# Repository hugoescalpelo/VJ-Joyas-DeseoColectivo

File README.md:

# VJ-Joyas-DeseoColectivo
Este repositorio contiene el código de la Máquina de deseo colectivo, un proyecto de VJ-Joyas

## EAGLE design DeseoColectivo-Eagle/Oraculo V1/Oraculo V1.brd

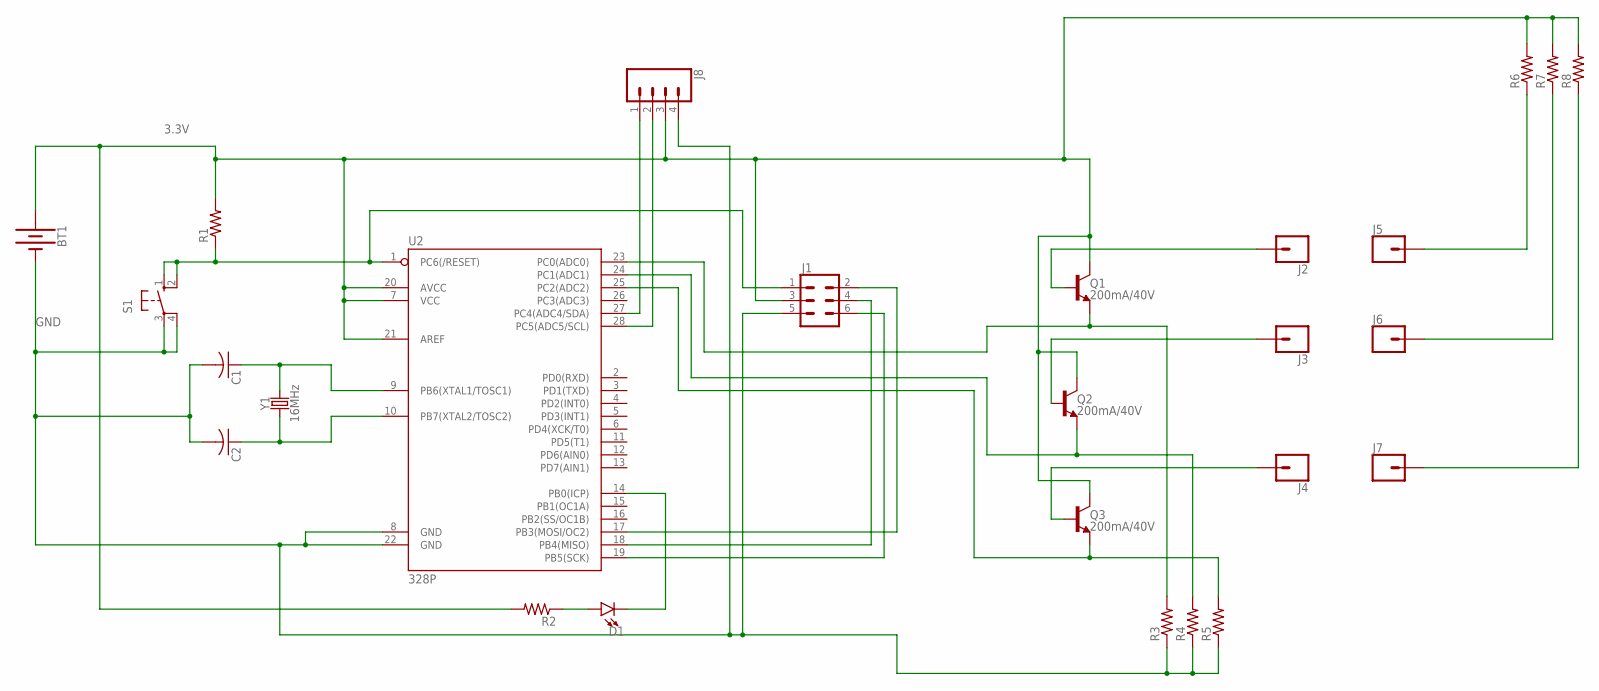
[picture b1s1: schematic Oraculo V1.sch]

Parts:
BT1: BATTERY-20MM_PTH; BATTCOM_20MM_PTH
C1, C2: C-US050-025X075; C050-025X075
D1: LED5MM; LED_5MM
J1: CONN_03X2NO_SILK; 2X3-NS
J2, J3, J4, J5, J6, J7: CONN_01; 1X01
J8: CONN_04; 1X04
Q1, Q2, Q3: 200mA/40V; TO-92
R1, R2, R3, R4, R5, R6, R7, R8: R-US_0204/7; 0204/7
S1: 10-XX; B3F-10XX
U2: 328P; DIP28
Y1: 16MHz; HC49US

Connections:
3.3V: BT1.1 (+), J1.3, J8.3, Q1.3 (C), Q2.3 (C), Q3.3 (C), R1.2, R2.2, R6.2, R7.2, R8.2, U2.7 (VCC), U2.20 (AVCC), U2.21 (AREF)
GND: BT1.2 (-), C1.2, C2.2, J1.5, J8.4, R3.1, R4.1, R5.1, S1.3, S1.4 (P1), U2.8 (GND), U2.22 (GND)
unnamed: C1.1, U2.9 (PB6(XTAL1/TOSC1)), Y1.2
unnamed: C2.1, U2.10 (PB7(XTAL2/TOSC2)), Y1.1
unnamed: J1.1, R1.1, S1.1 (S), S1.2 (S1), U2.1 (PC6(/RESET))
unnamed: J1.2, U2.17 (PB3(MOSI/OC2))
unnamed: D1.K (C), U2.14 (PB0(ICP))
unnamed: J1.6, U2.19 (PB5(SCK))
unnamed: J1.4, U2.18 (PB4(MISO))
unnamed: D1.A, R2.1
unnamed: J8.1, U2.27 (PC4(ADC4/SDA))
unnamed: J2.1, Q1.2 (B)
unnamed: J3.1, Q2.2 (B)
unnamed: J4.1, Q3.2 (B)
unnamed: Q1.1 (E), R3.2, U2.23 (PC0(ADC0))
unnamed: Q2.1 (E), R4.2, U2.24 (PC1(ADC1))
unnamed: Q3.1 (E), R5.2, U2.25 (PC2(ADC2))
unnamed: J5.1, J6.1, J7.1, R6.1, R7.1, R8.1
unnamed: J8.2, U2.28 (PC5(ADC5/SCL))

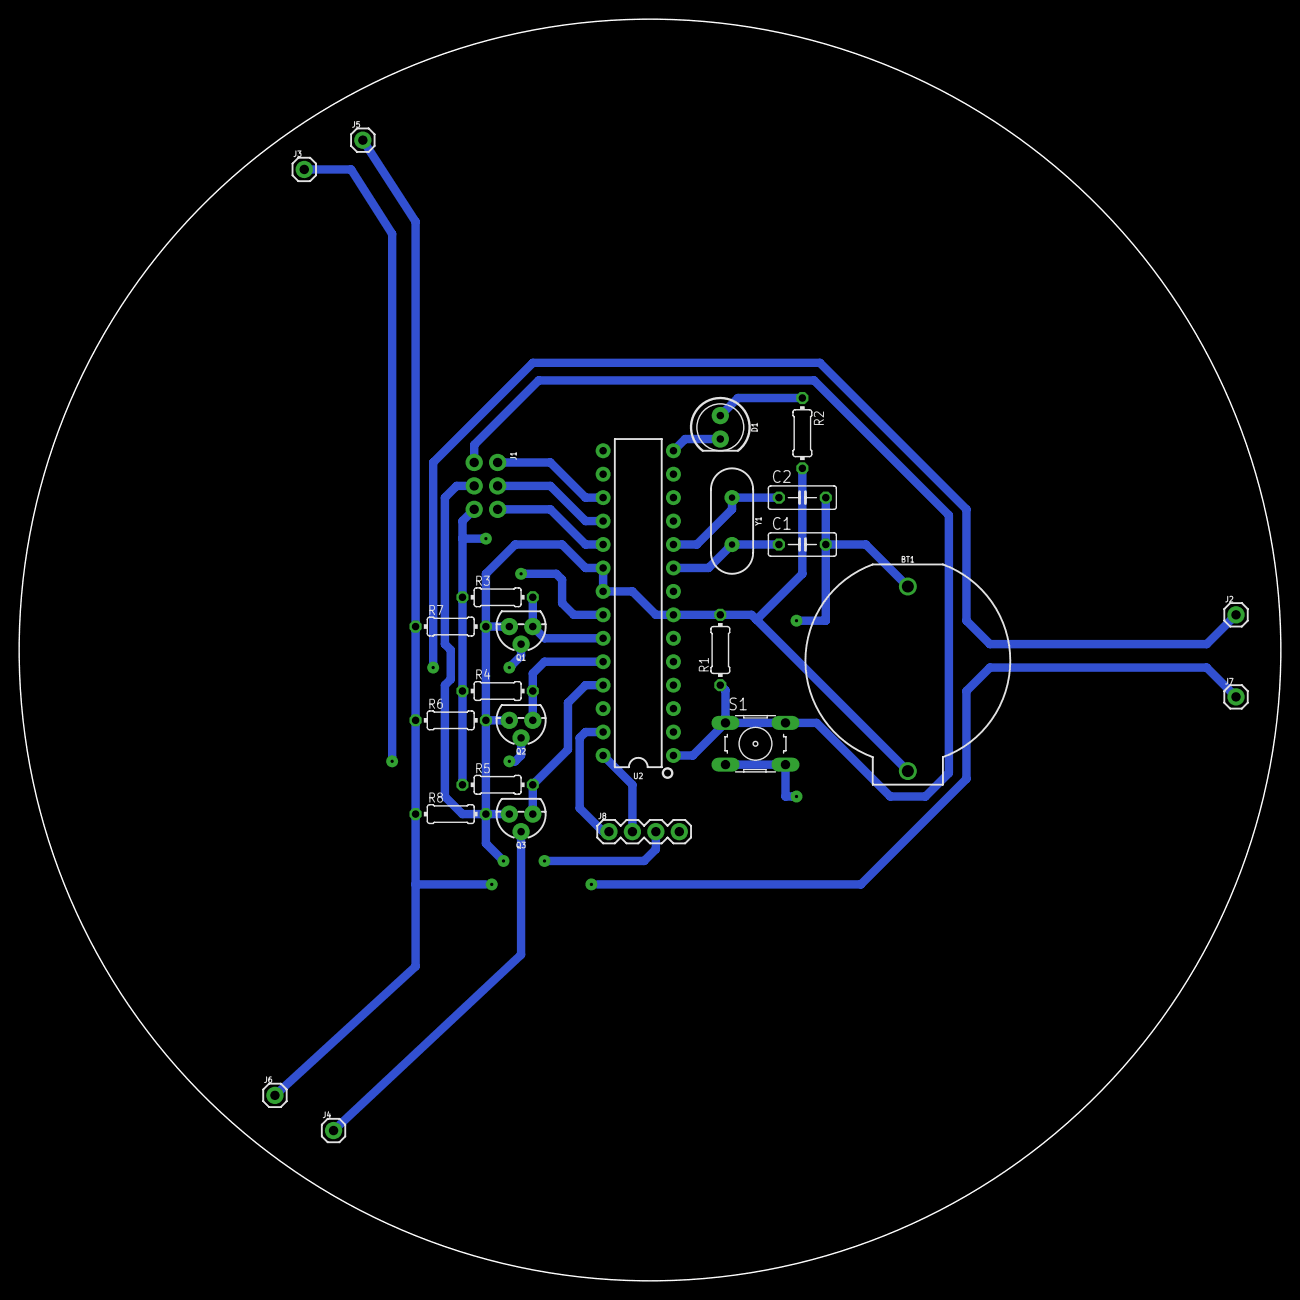
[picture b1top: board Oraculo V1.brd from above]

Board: 2 copper layers, 136.7 x 136.7 mm, 26 parts (0 on the bottom side), 19 nets.

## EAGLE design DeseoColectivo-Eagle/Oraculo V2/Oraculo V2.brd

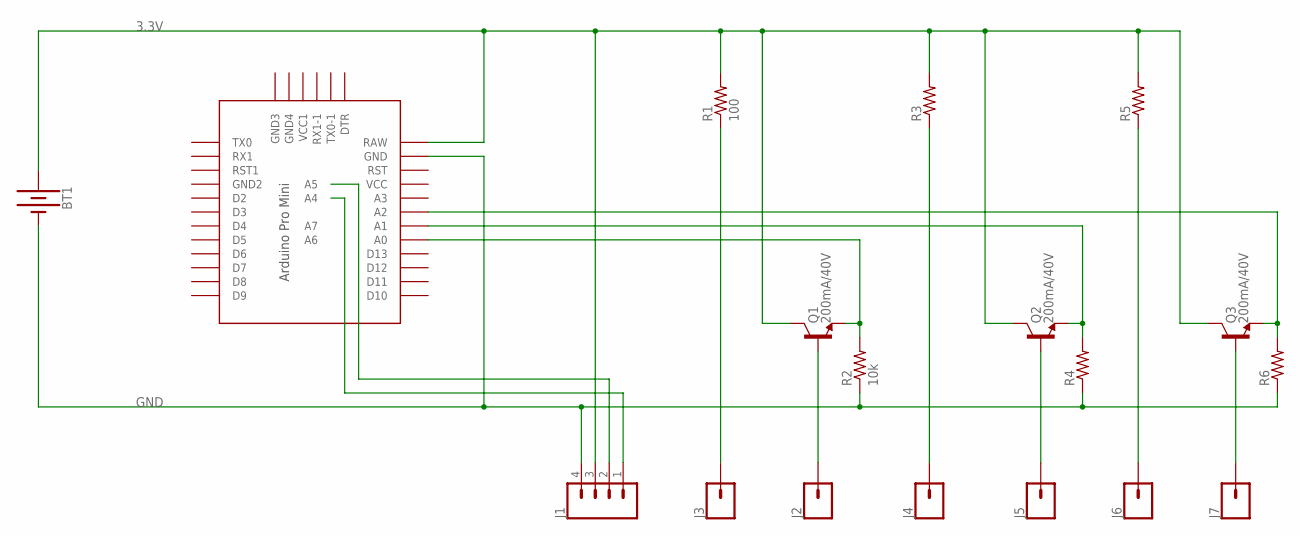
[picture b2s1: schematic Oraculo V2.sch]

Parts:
BT1: BATTERY-20MM_PTH; BATTCOM_20MM_PTH
J1: CONN_04; 1X04
J2, J3, J4, J5, J6, J7: CONN_01PTH_2MM; 1X01_2MM
Q1, Q2, Q3: 200mA/40V; TO-92
R1: 100; 0204/7
R2: 10k; 0204/7
R3, R4, R5, R6: R-US_0204/7; 0204/7
U$1: PRO-MINI-2

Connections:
3.3V: BT1.1 (+), J1.3, Q1.3 (C), Q2.3 (C), Q3.3 (C), R1.2, R3.2, R5.2, U$1.RAW
GND: BT1.2 (-), J1.4, R2.1, R4.1, R6.1, U$1.GND
unnamed: J1.2, U$1.A5
unnamed: J1.1, U$1.A4
unnamed: Q1.1 (E), R2.2, U$1.A0
unnamed: J2.1, Q1.2 (B)
unnamed: J3.1, R1.1
unnamed: J4.1, R3.1
unnamed: J7.1, Q3.2 (B)
unnamed: J5.1, Q2.2 (B)
unnamed: Q2.1 (E), R4.2, U$1.A1
unnamed: Q3.1 (E), R6.2, U$1.A2
unnamed: J6.1, R5.1

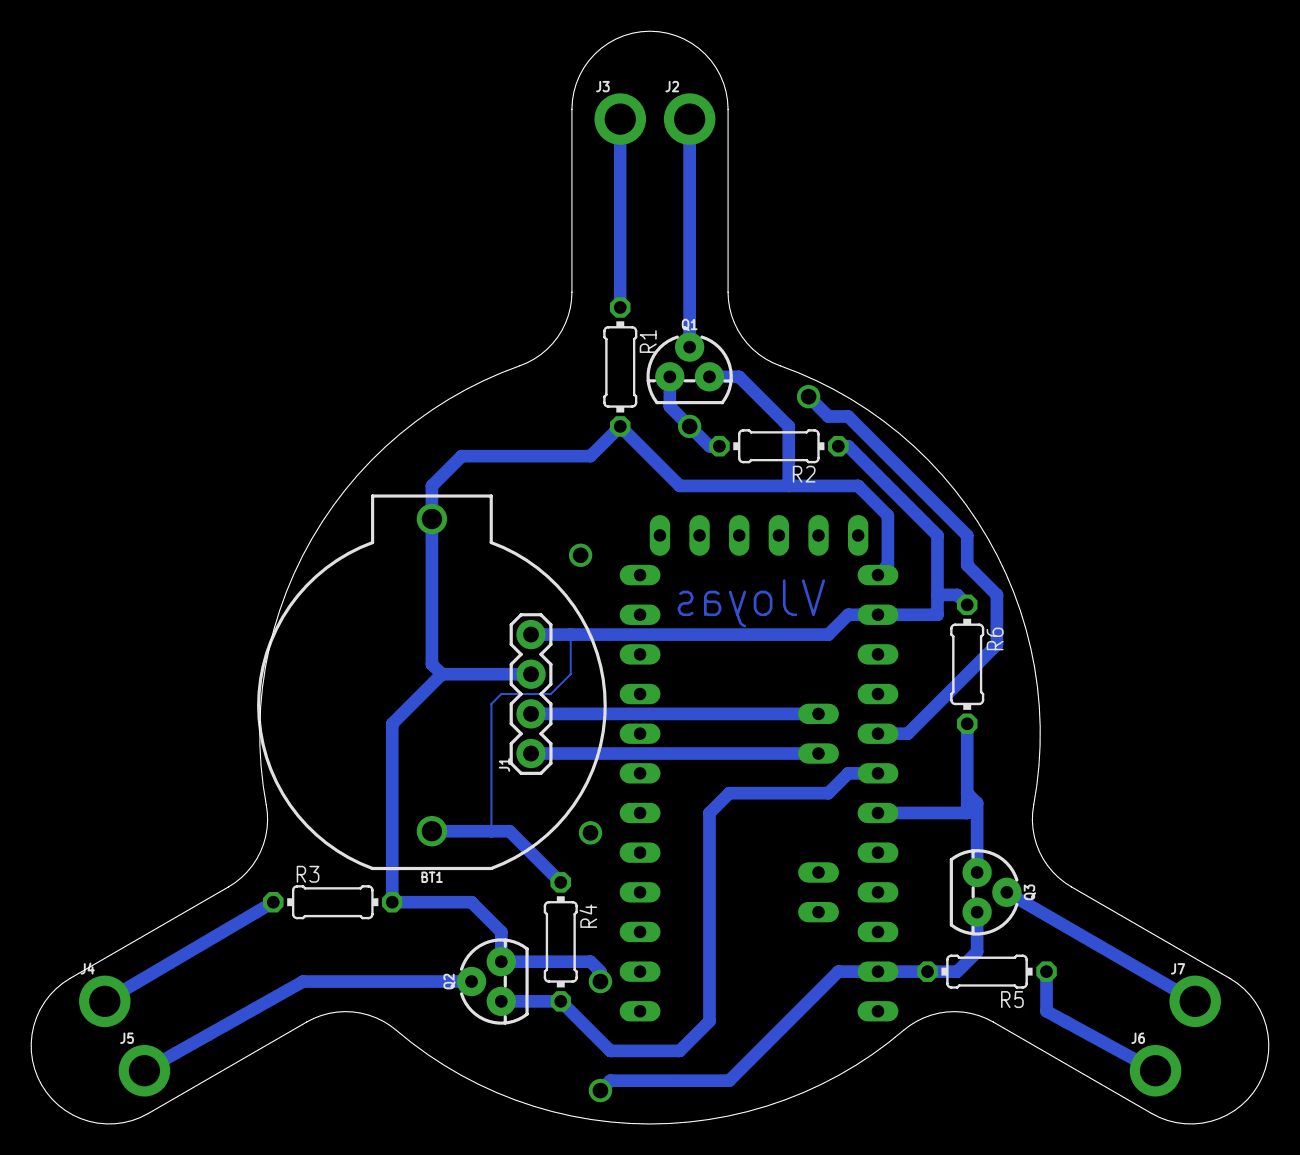
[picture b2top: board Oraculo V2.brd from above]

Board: 2 copper layers, 79.3 x 70.0 mm, 18 parts (0 on the bottom side), 13 nets.

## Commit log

2021-09-23 FirstCommit
    Changes added by Milena Pafundi and Hugo Vargas

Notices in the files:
parts and their libraries:
SparkFun-Batteries: Licensing: Creative Commons ShareAlike 4.0 International - https://creativecommons.org/licenses/by-sa/4.0
